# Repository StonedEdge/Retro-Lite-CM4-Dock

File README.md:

<div align="center">

# **Retro Lite CM4 AIO Docking Station**

</div>

# Description 
Updated: 2023/07/09

Note: Code base is now functional in terms of splashscreen, statistics images and metadata with text wrap! 
I'm considering this project completed at this stage. Feel free to make improvements to it and use it in any way you'd like! 

-----------------------------------------------------------------------------------------------------------

The Retro Lite CM4 docking station/hub is designed to be used with the Retro Lite CM4 gaming console however will work on any generic Linux host running RetroPie. 
The main goal of this project is to act as a metadata box for your RetroPie system & learn more about the games you are playing in real time - the aim is to preserve a small part of retro gaming history through this project. The project boasts the following features:

- Fully integrated 1.5" 128x128 SPI driven 16-bit color display 
- 3 modes, including **splashscreen**, **stats** and **game** mode. Navigation is done using a push button connected to a GPIO pin
- 3 x external USB 2.0 ports to use for keyboard, mouse & other peripherals in desktop mode. USB controller compatible for low latency
- USB-C charging 
- HDMI video output 

Here is the general flow of the program and how it works when power is applied:

1) **Splashscreen mode**
   - Splashscreen is played until EmulationStation starts. After which, stats mode is entered
2) **Stats mode**
   - Shows general system statistics - IP address, SoC temperature, RAM usage, etc. Stats are updated in 5 second intervals
   - Retro stats - see your systems overall top 5 games played by (a) duration and (b) times played 
3) **Game mode**
   - Shows a combined image of the game being played on launch of any game
   - Cycle through 5 different metadata views via the push button attached to the docking station. These are: 

         a) Combined vector image of wheel and screenshot

         b) Official game boxart

         c) A randomized vector image of the real hardware the game could be played on. Includes all variants of every console (shoutouts to Ampersand for providing the high quality vectors!)

         d) A description of the game, which scrolls vertically along the display

         e) Other metadata, including rating, release date, developer, publisher, genre & # players per game 

# Installation
To install, run (won't currently work yet!)
```
git clone https://github.com/StonedEdge/Retro-Lite-CM4-Dock.git
sudo chmod +x install_dock.sh
./ install_dock.sh
```

I recommend scraping your media files via the inbuilt scraper in the RetroPie setup script menus. This will download all of the metadata required and automatically store it in /home/pi/RetroPie/roms/{system_name}/media. 

# Metadata directory locations 

a) **Current game cover (boxart)** - /opt/retropie/configs/all/emulationstation/downloaded_images/{system}/{rom_name}.png

b) **Screenshot + combined wheel image** - /home/pi/retropie/roms/{system}/media/wheel/{rom_name}.png && /home/pi/retropie/roms/{system}/media/screenshot/{rom_name}.png

c) **Randomized vector images of console released** - /home/pi/pico/pico-examples/pico-spi/consolevectors

d) **Game description using vertical scrolling** - /opt/retropie/configs/all/emulationstation/gamelists', system_name, 'gamelist.xml'

e) **Game developer** - /opt/retropie/configs/all/emulationstation/gamelists', system_name, 'gamelist.xml' 

f) **Release date** - /opt/retropie/configs/all/emulationstation/gamelists', system_name, 'gamelist.xml'

g) **Videos** - /home/pi/retropie/roms/{system}/media/videos/{rom_name}.mp4

# Hardware 

Pinout to connect the OLED screen to the docking station is located above. Gerbers and CAD (both docking station and separate OLED box) files will be updated soon once the software is completed. 

# To-do
- [x] Detect current game/system booted using `runcommand`
- [x] Add Retrolite CM4 splashscreen on boot 
- [x] Downscale + convert screenshot and wheel images to 128x128 RGB565 on Pi 4 (Python)
- [x] Detect RP2040 by Product/Vendor IDs (VID/PIDs)  
- [x] Identify how to extract game text metadata using Python 
- [x] Send system stats to RP2040 over USB 
- [x] Clear buffer when runcommand-onend.sh is executed when a game is closed, bringing back user to Pi stats view
- [x] Stop splashscreen on COM port detect and switch to stats mode
- [x] Send over RGB565 combined.png over serial without corruption, automatic switching from Pi stats to current game
- [x] Write a python script to scale the boxart correctly to fit the screen
- [x] Send over random image to Pico located in consolevectors based on current system being launched on RetroPie (no scaling necessary)
- [x] Implement a button state machine to switch between the stats and image mode
- [x] Implement a timeout which fades black to the OLED with no button input. Wake up OLED on button press after X mins of no activity 
- [x] Implement game metadata within game mode
- [x] Gracefully shutdown the OLED display when the console is powered down and restart it when console is repowered on
- [x] Identify how to perform hardware (or software) vertical scrolling of text on the SSD1351 for game descriptions 
- [x] Fix some new line errors in metadata mode 
- [x] Figure out how to encode special characters - probably via European code pages (CP1250/1252)

# Nice to have/probably won't implement any time soon! 
- [ ] Write a python script to break up video into individual video frames on the Pi 4 
- [ ] Setup tinyUSB library to try and achieve 0.9MB/s transfer speeds for all frames, for 30 FPS video over USB 1.1 (max 1.5MB/s)
- [ ] Implement "retrostats" into stats mode to show user most played games by **times played** & **time duration** using the RetroStats scripts. Note : No RTC so time duration may not be accurate.

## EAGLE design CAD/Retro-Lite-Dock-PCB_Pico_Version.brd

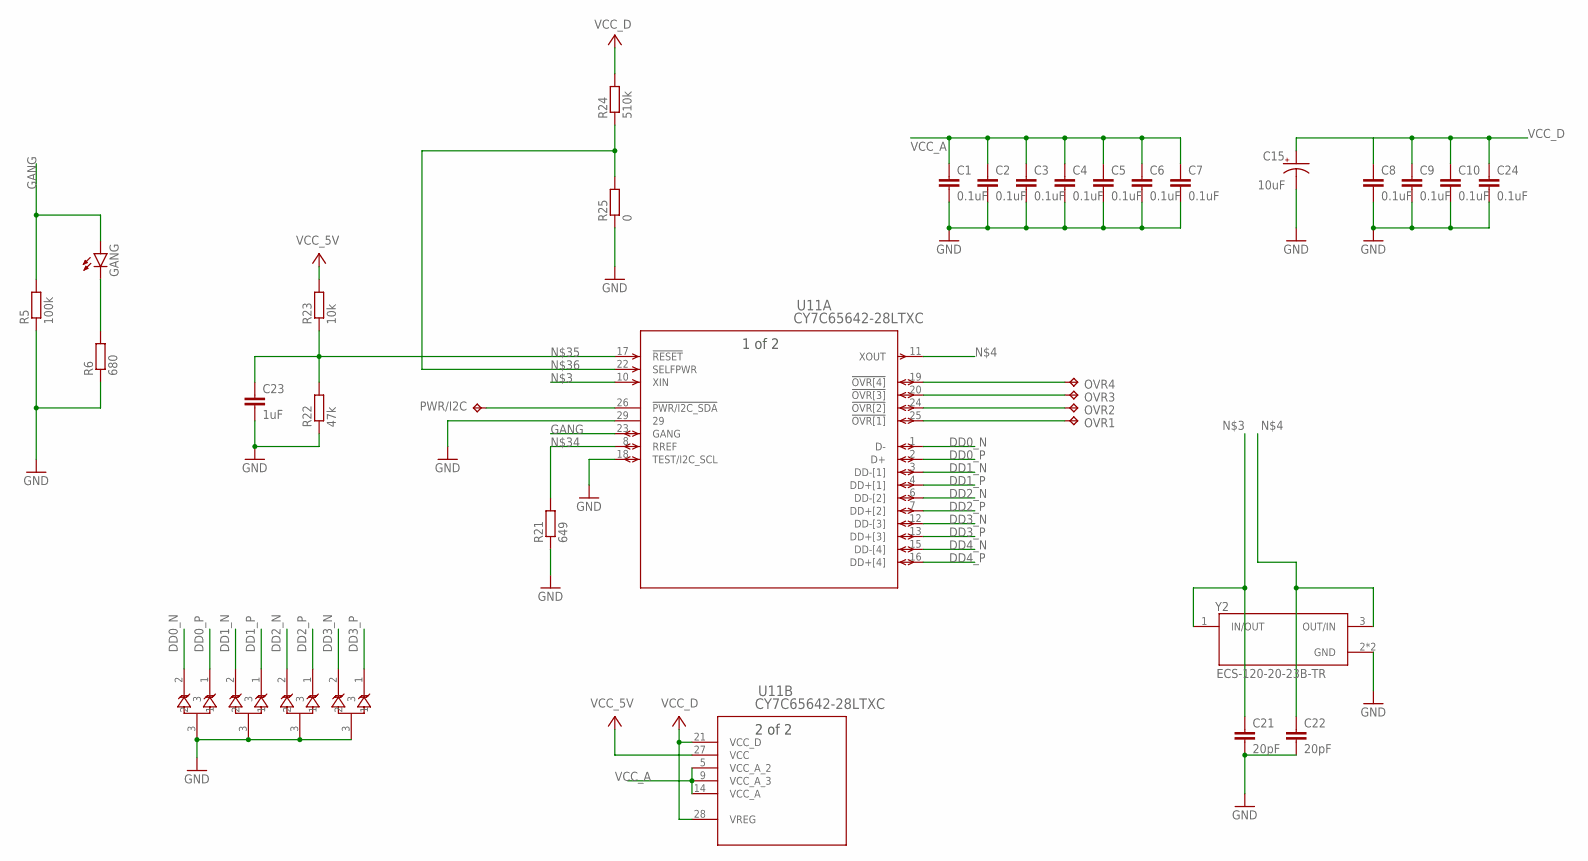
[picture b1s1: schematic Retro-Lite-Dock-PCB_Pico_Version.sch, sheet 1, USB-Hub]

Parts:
C1, C2, C3, C4, C5, C6, C7, C8, C9, C10, C24: 0.1uF; C0603
C15: 10uF; CAPAE660X610
C21, C22: 20pF; C0603
C23: 1uF; C0603
GANG: LEDSML0603; SML0603
OVR1, OVR2, OVR3, OVR4: TPTP09R; TP09R
PWR/I2C: TPTP09R; TP09R
R5: 100k; R0603
R6: 680; R0603
R21: 649; R0603
R22: 47k; R0603
R23: 10k; R0603
R24: 510k; R0603
R25: 0; R0603
U2, U3, U4, U10: RCLAMP0582BQTCT; SC75-3L_SEM
U11: CY7C65642-28LTXC; QFN-28
Y2: ECS-120-20-23B-TR; XTAL_ECS-120-20-23B-TR

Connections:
DD0_N: U10.2, U11.1 (D-); also elsewhere on the board
DD0_P: U10.1, U11.2 (D+); also elsewhere on the board
DD1_N: U2.2, U11.3 (DD-[1]); also elsewhere on the board
DD1_P: U2.1, U11.4 (DD+[1]); also elsewhere on the board
DD2_N: U3.2, U11.6 (DD-[2]); also elsewhere on the board
DD2_P: U3.1, U11.7 (DD+[2]); also elsewhere on the board
DD3_N: U4.2, U11.12 (DD-[3]); also elsewhere on the board
DD3_P: U4.1, U11.13 (DD+[3]); also elsewhere on the board
DD4_N: U11.15 (DD-[4]); also elsewhere on the board
DD4_P: U11.16 (DD+[4]); also elsewhere on the board
GANG: GANG.A, R5.2, U11.23 (GANG)
GND: C1.2, C2.2, C3.2, C4.2, C5.2, C6.2, C7.2, C8.2, C9.2, C10.2, C15.2 (-), C21.2, C22.2, C23.2, C24.2, R5.1, R6.1, R21.1, R22.1, R25.1, U2.3, U3.3, U4.3, U10.3, U11.18 (TEST/I2C_SCL), U11.29, Y2.2 (GND), Y2.4 (GND); also elsewhere on the board
unnamed: GANG.C, R6.2
unnamed: C21.1, U11.10 (XIN), Y2.1 (IN/OUT)
unnamed: C22.1, U11.11 (XOUT), Y2.3 (OUT/IN)
unnamed: OVR1.TP, U11.25 (!OVR[1])
unnamed: OVR2.TP, U11.24 (!OVR[2])
unnamed: OVR3.TP, U11.20 (!OVR[3])
unnamed: OVR4.TP, U11.19 (!OVR[4])
unnamed: R21.2, U11.8 (RREF)
unnamed: C23.1, R22.2, R23.1, U11.17 (!RESET)
unnamed: R24.1, R25.2, U11.22 (SELFPWR)
PWR/I2C_SDA: PWR/I2C.TP, U11.26 (!PWR/I2C_SDA)
VCC_5V: R23.2, U11.27 (VCC); also elsewhere on the board
VCC_A: C1.1, C2.1, C3.1, C4.1, C5.1, C6.1, C7.1, U11.5 (VCC_A_2), U11.9 (VCC_A_3), U11.14 (VCC_A); also elsewhere on the board
VCC_D: C8.1, C9.1, C10.1, C15.1 (+), C24.1, R24.2, U11.21 (VCC_D), U11.28 (VREG); also elsewhere on the board

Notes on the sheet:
10uF

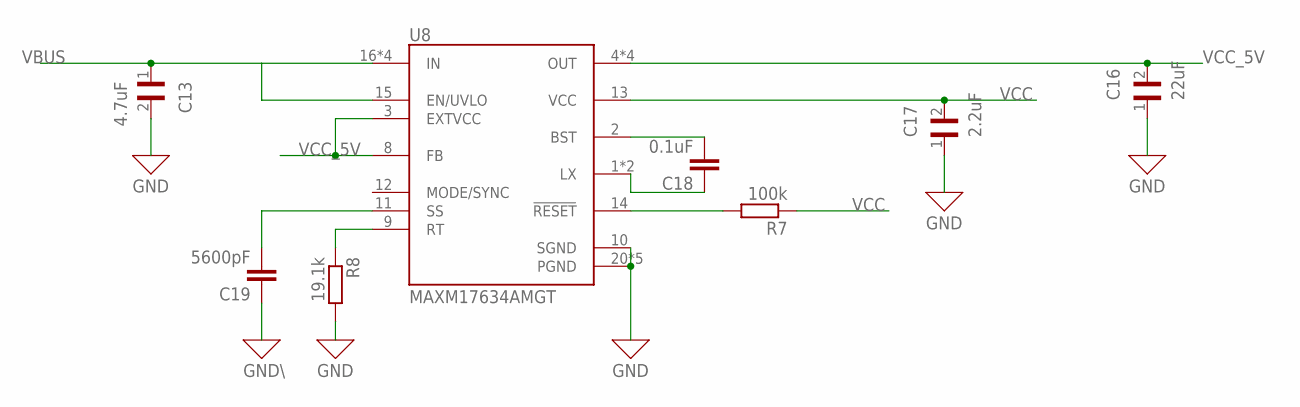
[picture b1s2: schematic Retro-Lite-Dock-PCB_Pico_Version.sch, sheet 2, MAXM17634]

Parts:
C13: 4.7uF; CAPC3216X180N
C16: 22uF; CAPC3225X270N
C17: 2.2uF; CAPC1608X90N
C18: 0.1uF; C0603
C19: 5600pF; C0603
R7: 100k; R0603
R8: 19.1k; R0603
U8: MAXM17634AMGT; QFN50P400X400X180-25N

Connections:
GND: C13.2, C16.1, C17.1, R8.2, U8.10 (SGND), U8.20 (PGND), U8.21 (PGND), U8.22 (PGND), U8.23 (PGND), U8.25 (PGND); also elsewhere on the board
GND\: C19.1
unnamed: R7.2, U8.14 (!RESET!)
unnamed: C18.2, U8.2 (BST)
unnamed: C18.1, U8.1 (LX), U8.24 (LX)
unnamed: C19.2, U8.11 (SS)
unnamed: R8.1, U8.9 (RT)
VBUS: C13.1, U8.15 (EN/UVLO), U8.16 (IN), U8.17 (IN), U8.18 (IN), U8.19 (IN); also elsewhere on the board
VCC: C17.2, R7.1, U8.13 (VCC)
VCC_5V: C16.2, U8.3 (EXTVCC), U8.4 (OUT), U8.5 (OUT), U8.6 (OUT), U8.7 (OUT), U8.8 (FB); also elsewhere on the board

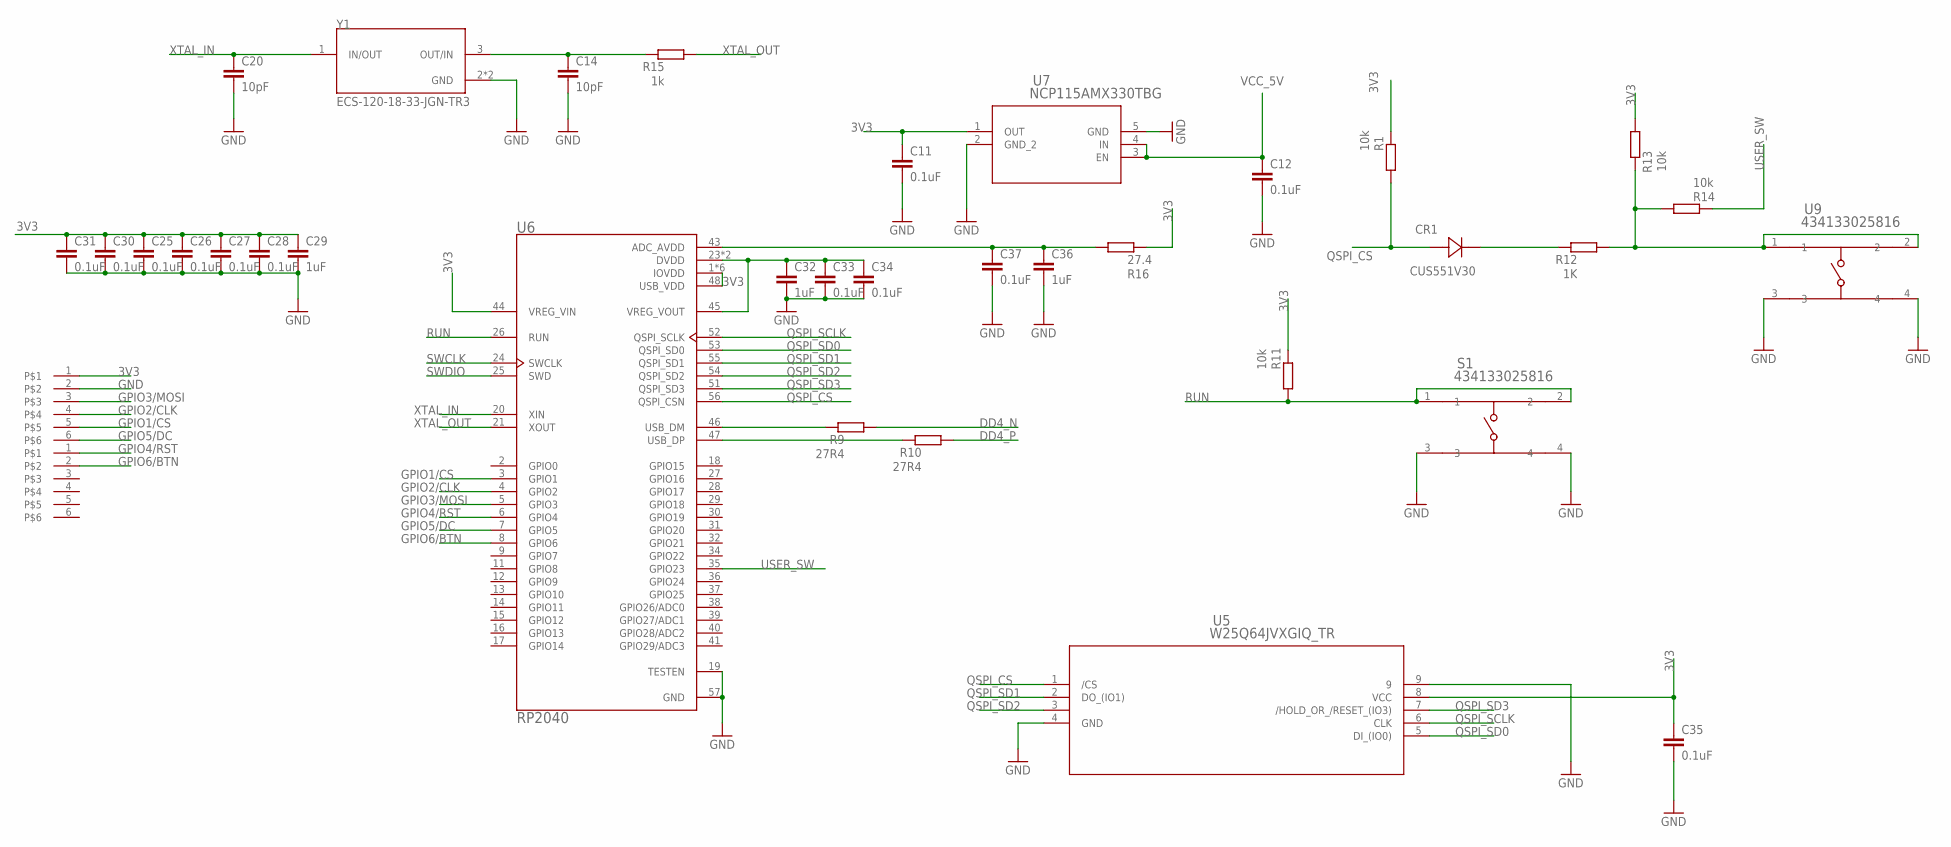
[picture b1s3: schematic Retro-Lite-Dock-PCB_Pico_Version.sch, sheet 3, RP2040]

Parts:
C11, C12, C25, C26, C27, C28, C31, C34, C35: 0.1uF; C0603
C14, C20: 10pF; C0603
C29, C36: 1uF; C0402
C30, C33, C37: 0.1uF; C0402
C32: 1uF; C0603
CR1: CUS551V30; USC_TOS
R1, R11, R13, R14: 10k; R0603
R9, R10: 27R4; R0402
R12: 1K; R0603
R15: 1k; R0402
R16: 27.4; R0402
S1: 434133025816; SMD_025816_WRE
U5: W25Q64JVXGIQ_TR; DFN_XGIQ_TR_WIN
U6: RP2040; QFN40P700X700X90-57N
U7: NCP115AMX330TBG; XDFN4_711AJ_ONS
U9: 434133025816; SMD_025816_WRE
U$2, U$3: 6PINEADER; 1MM_PIC-PROGRAMING_HEADER
Y1: ECS-120-18-33-JGN-TR3; XTAL_ECS-120-18-33-JGN-TR3

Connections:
3V3: C11.1, C25.1, C26.1, C27.1, C28.1, C29.1, C30.1, C31.1, C35.1, R1.2, R11.2, R13.1, R16.2, U5.8 (VCC), U6.1 (IOVDD), U6.10 (IOVDD), U6.22 (IOVDD), U6.33 (IOVDD), U6.42 (IOVDD), U6.44 (VREG_VIN), U6.48 (USB_VDD), U6.49 (IOVDD), U7.1 (OUT), U$3.1
DD4_N: R9.1; also elsewhere on the board
DD4_P: R10.1; also elsewhere on the board
GND: C11.2, C12.2, C14.2, C20.2, C25.2, C26.2, C27.2, C28.2, C29.2, C30.2, C31.2, C32.2, C33.2, C34.2, C35.2, C36.2, C37.2, S1.3, S1.4, U5.4 (GND), U5.9, U6.19 (TESTEN), U6.57 (GND), U7.2 (GND_2), U7.5 (GND), U9.3, U9.4, U$3.2, Y1.2 (GND), Y1.4 (GND); also elsewhere on the board
GPIO1/CS: U6.3 (GPIO1), U$3.5
GPIO2/CLK: U6.4 (GPIO2), U$3.4
GPIO3/MOSI: U6.5 (GPIO3), U$3.3
GPIO4/RST: U6.6 (GPIO4), U$2.1
GPIO5/DC: U6.7 (GPIO5), U$3.6
GPIO6/BTN: U6.8 (GPIO6), U$2.2
unnamed: C32.1, C33.1, C34.1, U6.23 (DVDD), U6.45 (VREG_VOUT), U6.50 (DVDD)
unnamed: R9.2, U6.46 (USB_DM)
unnamed: R10.2, U6.47 (USB_DP)
unnamed: R12.1, R13.2, R14.1, U9.1, U9.2
unnamed: C14.1, R15.2, Y1.3 (OUT/IN)
unnamed: C36.1, C37.1, R16.1, U6.43 (ADC_AVDD)
unnamed: CR1.1 (CATHODE), R12.2
QSPI_CS: CR1.2 (ANODE), R1.1, U5.1 (/CS), U6.56 (QSPI_CSN)
QSPI_SCLK: U5.6 (CLK), U6.52 (QSPI_SCLK)
QSPI_SD0: U5.5 (DI_(IO0)), U6.53 (QSPI_SD0)
QSPI_SD1: U5.2 (DO_(IO1)), U6.55 (QSPI_SD1)
QSPI_SD2: U5.3 (/WP_(IO2)), U6.54 (QSPI_SD2)
QSPI_SD3: U5.7 (/HOLD_OR_/RESET_(IO3)), U6.51 (QSPI_SD3)
RUN: R11.1, S1.1, S1.2, U6.26 (RUN)
SWCLK: U6.24 (SWCLK); also elsewhere on the board
SWDIO: U6.25 (SWD); also elsewhere on the board
USER_SW: R14.2, U6.35 (GPIO23)
VCC_5V: C12.1, U7.3 (EN), U7.4 (IN); also elsewhere on the board
XTAL_IN: C20.1, U6.20 (XIN), Y1.1 (IN/OUT)
XTAL_OUT: R15.1, U6.21 (XOUT)

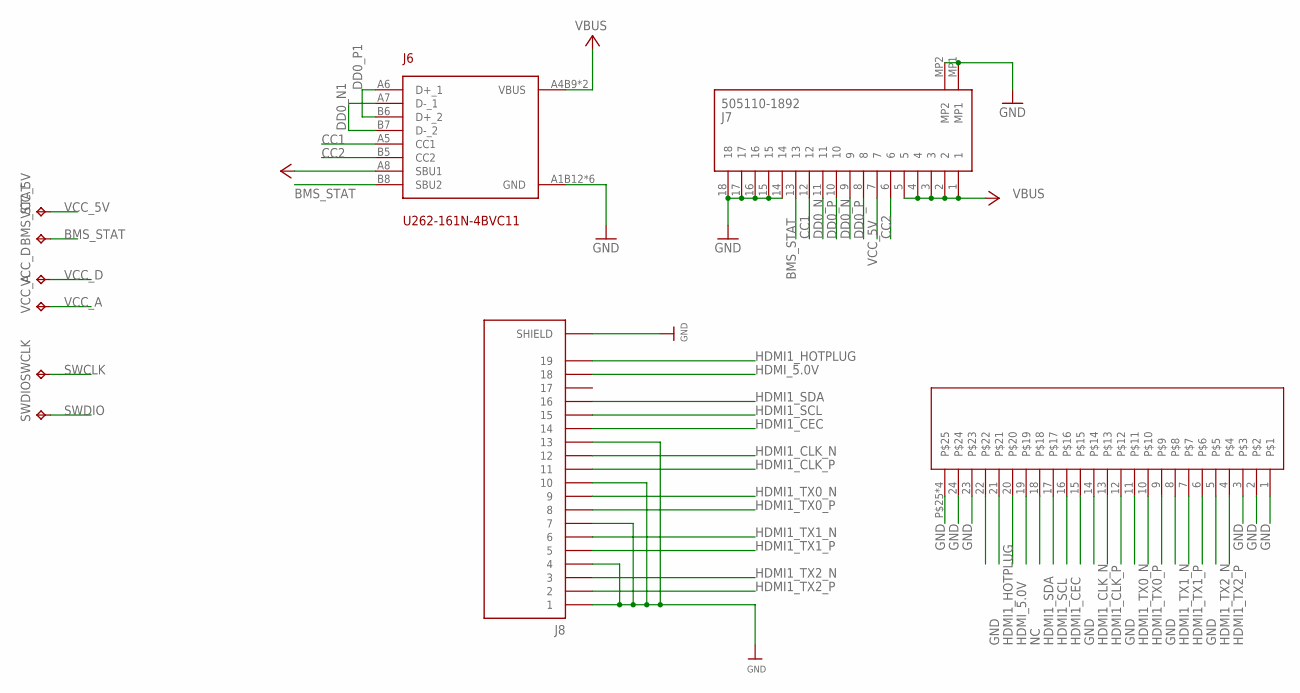
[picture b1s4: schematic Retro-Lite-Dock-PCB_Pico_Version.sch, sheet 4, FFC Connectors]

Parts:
BMS_STAT: TPTP09R; TP09R
J6: U262-161N-4BVC11
J7: 505110-1892; 5051101892
J8: 685119136923; WURTH_685119136923
SWCLK: TPTP09R; TP09R
SWDIO: TPTP09R; TP09R
U$1: 5022442430_FFC; 5022442430
VCC_5V: TPTP09R; TP09R
VCC_A: TPTP09R; TP09R
VCC_D: TPTP09R; TP09R

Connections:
BMS_STAT: BMS_STAT.TP, J6.B8 (SBU2), J7.13
CC1: J6.A5 (CC1), J7.12
CC2: J6.B5 (CC2), J7.6
DD0_N: J7.9, J7.11; also elsewhere on the board
DD0_N1: J6.A7 (D-_1), J6.B7 (D-_2)
DD0_P: J7.8, J7.10; also elsewhere on the board
DD0_P1: J6.A6 (D+_1), J6.B6 (D+_2)
GND: J6.A1B12 (GND), J6.B1A12 (GND), J6.SHIELD_1 (GND), J6.SHIELD_2 (GND), J6.SHIELD_3 (GND), J6.SHIELD_4 (GND), J7.14, J7.15, J7.16, J7.17, J7.18, J7.MP1, J7.MP2, J8.1, J8.4, J8.7, J8.10, J8.13, J8.S1 (SHIELD), J8.S2 (SHIELD), J8.S3 (SHIELD), J8.S4 (SHIELD), U$1.1, U$1.2, U$1.3, U$1.6, U$1.9, U$1.12, U$1.15, U$1.22, U$1.23, U$1.24, U$1.P$25, U$1.P$26, U$1.P$27, U$1.P$28; also elsewhere on the board
HDMI1_CEC: J8.14, U$1.16
HDMI1_CLK_N: J8.12, U$1.14
HDMI1_CLK_P: J8.11, U$1.13
HDMI1_HOTPLUG: J8.19, U$1.21
HDMI1_SCL: J8.15, U$1.17
HDMI1_SDA: J8.16, U$1.18
HDMI1_TX0_N: J8.9, U$1.11
HDMI1_TX0_P: J8.8, U$1.10
HDMI1_TX1_N: J8.6, U$1.8
HDMI1_TX1_P: J8.5, U$1.7
HDMI1_TX2_N: J8.3, U$1.5
HDMI1_TX2_P: J8.2, U$1.4
HDMI_5.0V: J8.18, U$1.20
NC: U$1.19
SWCLK: SWCLK.TP; also elsewhere on the board
SWDIO: SWDIO.TP; also elsewhere on the board
VBUS: J6.A4B9 (VBUS), J6.B4A9 (VBUS), J7.1, J7.2, J7.3, J7.4, J7.5; also elsewhere on the board
VCC_5V: J6.A8 (SBU1), J7.7, VCC_5V.TP; also elsewhere on the board
VCC_A: VCC_A.TP; also elsewhere on the board
VCC_D: VCC_D.TP; also elsewhere on the board

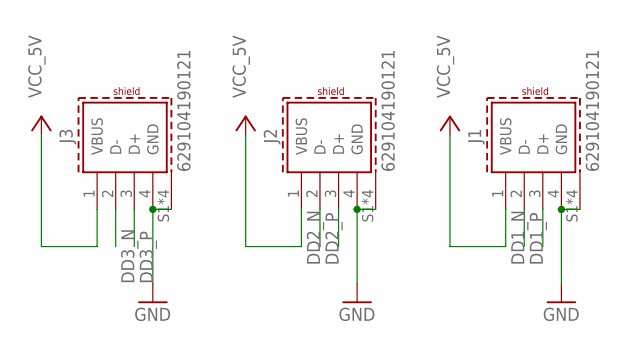
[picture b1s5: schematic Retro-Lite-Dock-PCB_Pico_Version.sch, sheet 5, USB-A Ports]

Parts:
J1, J2, J3: 629104190121

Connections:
DD1_N: J1.2 (D-); also elsewhere on the board
DD1_P: J1.3 (D+); also elsewhere on the board
DD2_N: J2.2 (D-); also elsewhere on the board
DD2_P: J2.3 (D+); also elsewhere on the board
DD3_N: J3.2 (D-); also elsewhere on the board
DD3_P: J3.3 (D+); also elsewhere on the board
GND: J1.4 (GND), J1.S1 (SHIELD), J1.S2 (SHIELD), J1.S3 (SHIELD), J1.S4 (SHIELD), J2.4 (GND), J2.S1 (SHIELD), J2.S2 (SHIELD), J2.S3 (SHIELD), J2.S4 (SHIELD), J3.4 (GND), J3.S1 (SHIELD), J3.S2 (SHIELD), J3.S3 (SHIELD), J3.S4 (SHIELD); also elsewhere on the board
VCC_5V: J1.1 (VBUS), J2.1 (VBUS), J3.1 (VBUS); also elsewhere on the board

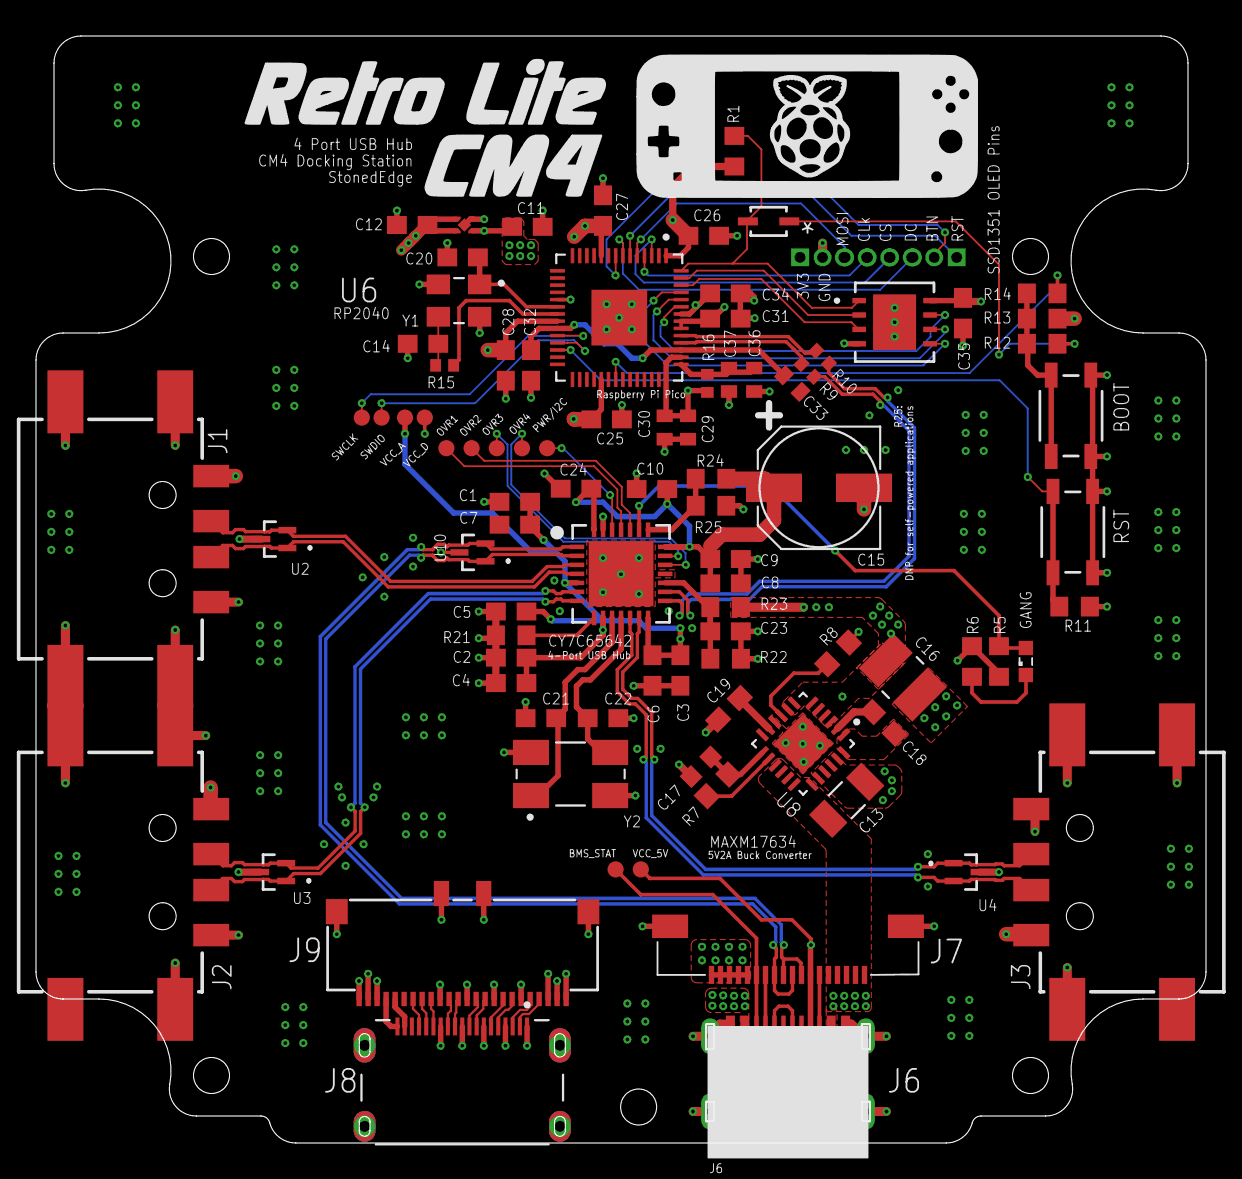
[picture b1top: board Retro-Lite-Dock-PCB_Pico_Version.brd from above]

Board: 4 copper layers, 64.9 x 61.4 mm, 90 parts (0 on the bottom side), 77 nets.

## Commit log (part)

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2023-02-04 Add source code files
2023-02-06 Add blocking wait delay to prevent lockup
2023-02-06 Upload game stats scripts
2023-02-06 Add sleep delay for dma_channel_wait_blocking
2023-02-09 Add stats script - Pi 4
    Monitor system parameters of the Pi 4 and send the data through serial connection (using the ser object).
2023-02-09 Indentation error fix
2023-02-09 Rename main.c to splashscreen.c
2023-02-10 Create LICENSE
2023-02-10 Add splashscreen func def
2023-02-10 Add function for extracting game metadata
2023-03-29 Fix parenthesis for receive_start_string
2023-03-30 Update pinout
2023-04-05 Upload python3 script to show system stats
2023-04-09 Set column and row address before updating
2023-04-13 Fix start, end and stop string func
    Fixed functions always returning true regardless of serial input value
2023-04-17 Remove boxart read_lines duplication
2023-04-17 Active low button press
2023-04-18 Update boxart scaling
2023-04-19 Add randomization for console images
2023-04-20 Allow for two picos to be connected at once (external display)
2023-04-21 Fix loop index for serial image reads
2023-04-25 Pullup button_pin 6
2023-05-01 Add serial file lock
2023-05-01 Add non-blocking serial lock
2023-05-08 Update game metadata function
2023-05-15 Pack image data to big endian format
2023-05-15 Implement sleep mode after min of inactivity
2023-05-16 Add metadata func
2023-05-22 Graceful shutdown on power off
2023-06-01 Fix shutdown and reboot issue
2023-06-02 Splashscreen on shutdown/message fix
2023-06-02 Splashscreen on shutdown/reboot fix
2023-06-02 Update LICENSE
2023-06-03 Shorten splashscreen length on power down
2023-06-04 Fix text centering & background issue
2023-06-05 Add game metadata variables
2023-06-12 Update install_dock.sh for RetroStats installation
2023-06-16 Fix x + 127 issue

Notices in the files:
parts and their libraries:
COPYRIGHT: Copyright (C) 2018 Accelerated Designs. All rights reserved
COPYRIGHT: Copyright (C) 2022 Ultra Librarian. All rights reserved.
microbuilder: This work is placed in the public domain, and may be freely used for commercial and non-commercial work with the following conditions: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
